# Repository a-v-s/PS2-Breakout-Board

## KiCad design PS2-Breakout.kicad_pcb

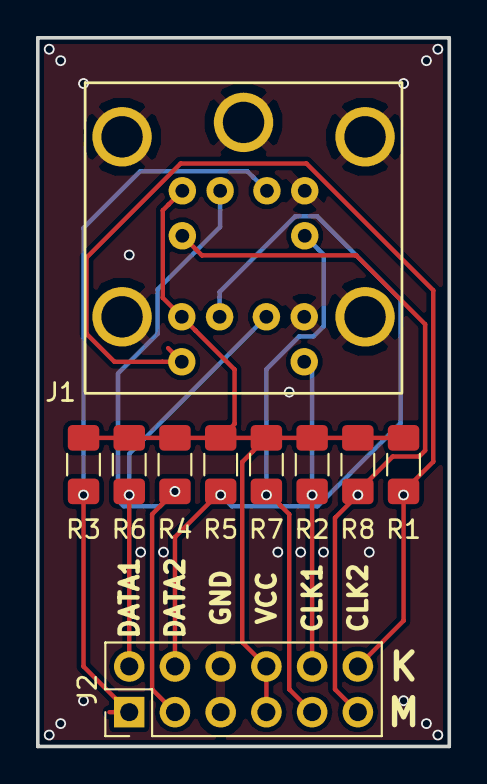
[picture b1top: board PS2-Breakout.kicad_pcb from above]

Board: 2 copper layers, 22.9 x 39.4 mm, 10 parts (0 on the bottom side), 10 nets.

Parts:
J1: Dual-Mini-DIN-6_0; DUAL-MINI-DIN-6-FULL-SHIELD
J2: Conn_02x06_Odd_Even; PinHeader_2x06_P2.54mm_Vertical
R1, R2, R3, R4, R5, R6, R7, R8: 10k; R_1206_3216Metric_Pad1.42x1.75mm_HandSolder

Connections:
K_CLK1: J1.5, J2.9, R7.2
K_CLK2: J1.6, J2.11, R8.2
K_DATA1: J1.1, J2.1, R3.2
K_DATA2: J1.2, J2.3, R4.2
K_GND: J1.3, J1.9, J1.13, J2.5, J2.6
K_VCC: J1.4, J1.10, J2.7, J2.8, R1.1, R2.1, R3.1, R4.1, R5.1, R6.1, R7.1, R8.1
M_CLK1: J1.11, J2.10, R2.2
M_CLK2: J1.12, J2.12, R1.2
M_DATA1: J1.7, J2.2, R6.2
M_DATA2: J1.8, J2.4, R5.2

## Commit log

2018-11-18 Modified for DUAL PS/2
